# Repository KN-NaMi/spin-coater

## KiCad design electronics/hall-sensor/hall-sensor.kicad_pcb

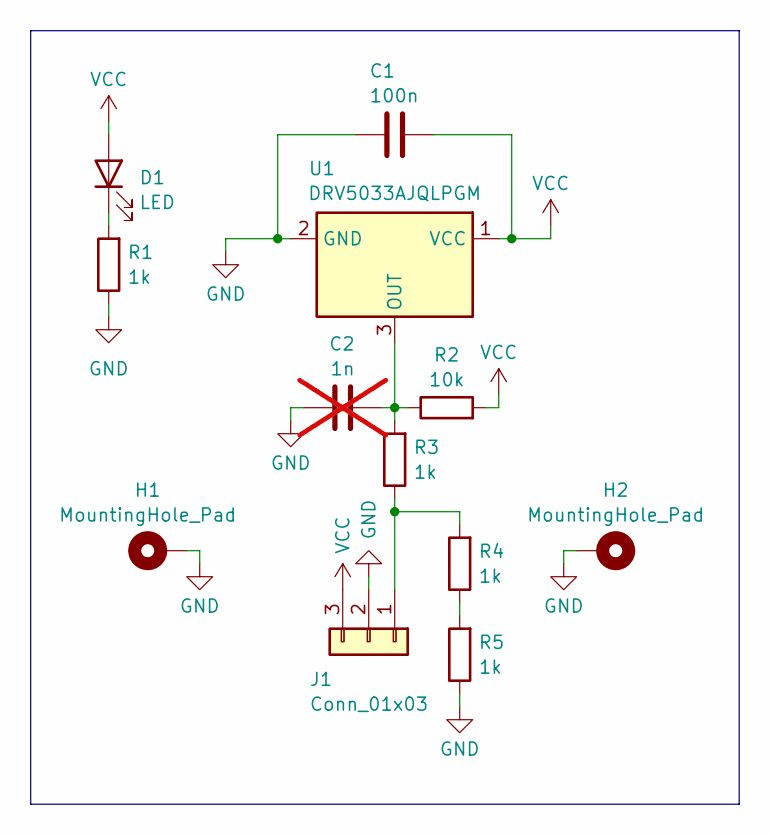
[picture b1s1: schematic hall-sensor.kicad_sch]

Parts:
C1: 100n; C_0805_2012Metric_Pad1.18x1.45mm_HandSolder
C2: 1n; C_0805_2012Metric_Pad1.18x1.45mm_HandSolder; not fitted
D1: LED; LED_1206_3216Metric
H1, H2: MountingHole_Pad; MountingHole_3.2mm_M3_Pad
J1: Conn_01x03; JST_XH_S3B-XH-A_1x03_P2.50mm_Horizontal
R1, R3, R4, R5: 1k; R_0805_2012Metric
R2: 10k; R_0805_2012Metric_Pad1.20x1.40mm_HandSolder
U1: DRV5033AJQLPGM; TO-92_Horizontal2

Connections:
GND: C1.2, C2.1, H1.1, H2.1, J1.2, R1.1, R5.1, U1.2 (GND)
unnamed: D1.1 (K), R1.2
unnamed: J1.1, R3.1, R4.2
unnamed: R4.1, R5.2
unnamed: C2.2, R2.1, R3.2, U1.3 (OUT)
VCC: C1.1, D1.2 (A), J1.3, R2.2, U1.1 (VCC)

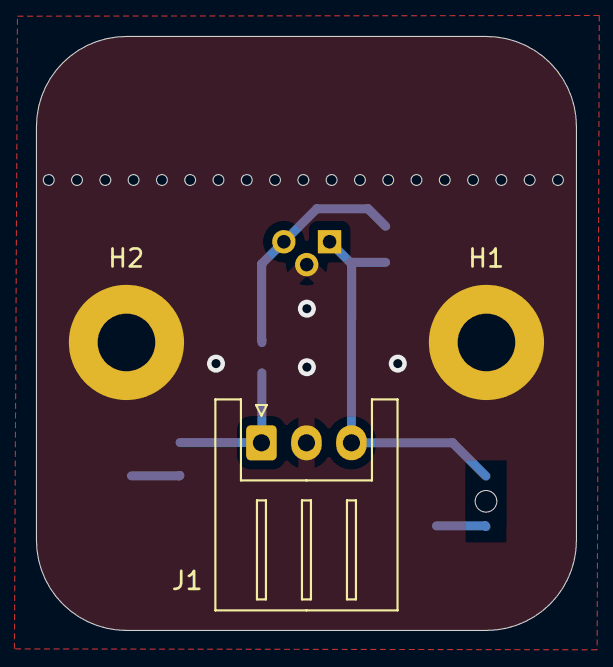
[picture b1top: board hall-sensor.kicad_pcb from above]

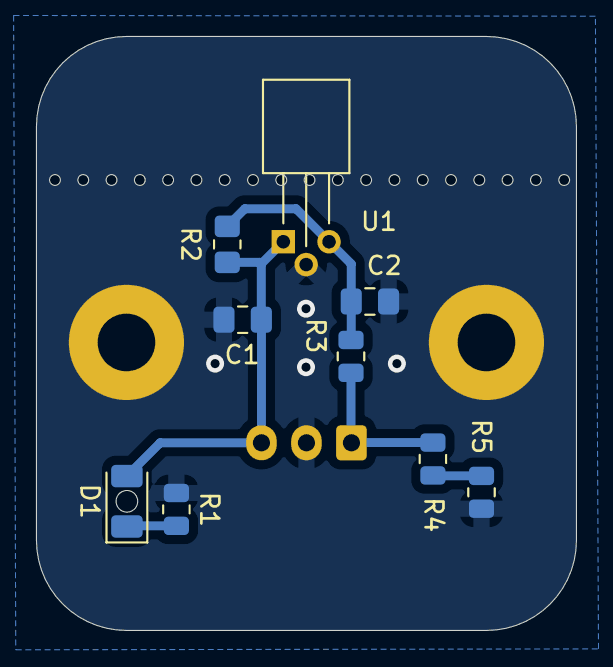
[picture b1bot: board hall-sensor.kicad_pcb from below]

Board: 2 copper layers, 30.0 x 33.0 mm, 12 parts (9 on the bottom side), 6 nets.

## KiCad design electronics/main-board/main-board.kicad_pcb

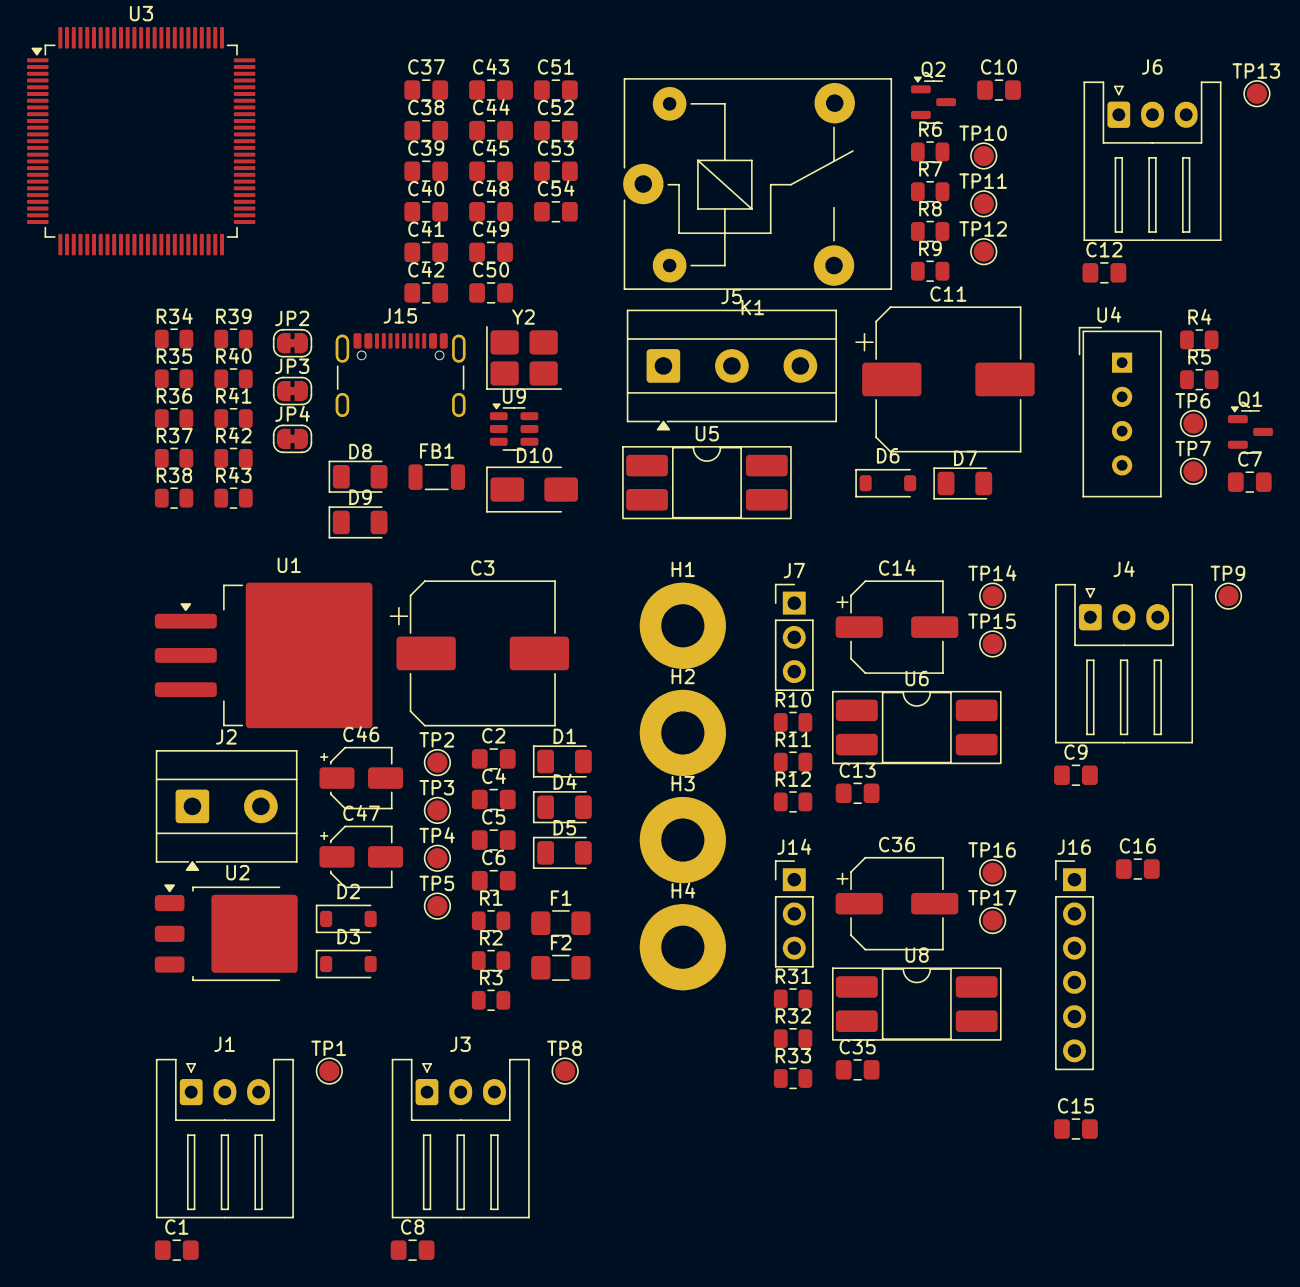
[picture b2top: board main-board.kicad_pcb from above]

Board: 2 copper layers, 120 parts (0 on the bottom side), 48 nets, no tracks yet.

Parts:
C1, C2, C4, C5, C6, C7, C8, C9, C10, C12, C13, C15, C16, C35, C37, C38, C39, C40, C41, C42, C43, C44, C45, C52: 100n; C_0805_2012Metric_Pad1.18x1.45mm_HandSolder
C3, C11: 220u; CP_Elec_10x10.5
C14, C36: 100u; CP_Elec_6.3x5.4
C46, C47: 10u; CP_Elec_4x5.4
C48, C49: 2n2; C_0805_2012Metric_Pad1.18x1.45mm_HandSolder
C50: 10p; C_0805_2012Metric_Pad1.18x1.45mm_HandSolder
C51: 20p; C_0805_2012Metric_Pad1.18x1.45mm_HandSolder
C53, C54: 470n; C_0805_2012Metric_Pad1.18x1.45mm_HandSolder
D1, D4, D5, D7, D8, D9: LED; LED_1206_3216Metric
D2, D3, D6: 1N4148W; D_SOD-123
D10: SS34; D_SMA
F1: 3A; Fuse_1206_3216Metric_Pad1.42x1.75mm_HandSolder
F2: 500mA; Fuse_1206_3216Metric_Pad1.42x1.75mm_HandSolder
FB1: FerriteBead; L_1206_3216Metric
H1, H2, H3, H4: MountingHole_Pad; MountingHole_3.2mm_M3_Pad
J1, J3, J4, J6: HALL-SENSOR; JST_XH_S3B-XH-A_1x03_P2.50mm_Horizontal
J2: 24V-IN; TerminalBlock_MetzConnect_Type101_RT01602HBWC_1x02_P5.08mm_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
J5: VACUME-PUMP; TerminalBlock_MetzConnect_Type101_RT01603HBWC_1x03_P5.08mm_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
J7, J14: SERVO_MOTOR-OUT; PinHeader_1x03_P2.54mm_Vertical
J15: SHOU HAN TYPE-C 16PIN 2MD; USB_C_Receptacle_GCT_USB4105-xx-A_16P_TopMnt_Horizontal
J16: UART; PinHeader_1x06_P2.54mm_Vertical
JP2, JP3, JP4: SolderJumper_2_Bridged; SolderJumper-2_P1.3mm_Bridged_RoundedPad1.0x1.5mm
K1: SRD-05VDC-SL-C; Relay_SPDT_SANYOU_SRD_Series_Form_C
Q1: BSS138; SOT-23
Q2: MMBT2222A; SOT-23
R1, R4, R5, R8, R9, R12, R33, R34, R35: 10k; R_0805_2012Metric
R2, R3, R7, R11, R32, R36, R37: 1k; R_0805_2012Metric
R6, R10, R31: 330; R_0805_2012Metric
R38, R39, R43: 0; R_0805_2012Metric
R40, R41: 5k1; R_0805_2012Metric
R42: 1M; R_0805_2012Metric
TP1, TP2, TP3, TP4, TP5, TP6, TP7, TP8, TP9, TP10, TP11, TP12, TP13, TP14, TP15, TP16, TP17: TestPoint; TestPoint_Pad_D1.5mm
U1: L7805; TO-263-3_TabPin2
U2: AMS1117CD-3.3; TO-252-3_TabPin2
U3: STM32F407V_E-G_Tx; LQFP-100_14x14mm_P0.5mm
U4: DHT11; Aosong_DHT11_5.5x12.0_P2.54mm
U5, U6, U8: EL817S1; DIP-4_W8.89mm_SMDSocket_LongPads
U9: SRV05-4; SOT-23-6
Y2: X322516MLB4SI; Crystal_SMD_3225-4Pin_3.2x2.5mm_HandSoldering

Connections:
+3V3: C1.2, C6.2, C8.2, C9.2, C12.2, C15.2, C16.2, C38.2, C39.2, C40.2, C41.2, C42.2, C43.2, C47.1, D3.2 (A), D5.2 (A), J1.1, J3.1, J4.1, J6.1, J16.2, J16.5, JP2.1 (A), JP3.1 (A), JP4.1 (A), Q1.1 (G), R4.2, R34.2, TP5.1, U2.2 (VO), U3.11 (VDD), U3.19 (VDD), U3.28 (VDD), U3.50 (VDD), U3.75 (VDD), U3.100 (VDD), U9.5 (VP)
+5V: C5.2, C7.2, C13.2, C14.1, C35.2, C36.1, C46.1, C53.2, D2.2 (A), D3.1 (K), D4.2 (A), D6.1 (K), J7.2, J14.2, K1.2, R5.2, R43.1, TP4.1, U1.3 (OUT), U2.3 (VI), U4.1 (VDD), U5.4, U6.4, U8.4
+24V: C10.2, C11.1, D1.2 (A), F1.2, K1.1, TP2.1
/DHT11/DHT11: Q1.2 (S), R4.1, TP6.1
/STM/BOOT: R35.2, U3.94 (BOOT0)
/STM/NRST: C37.2, R34.1, U3.14 (NRST)
/STM/USB_OTG_FS_DN: J15.A7 (D-), J15.B7 (D-), U3.70 (PA11), U9.3 (IO2), U9.6 (IO4)
/STM/USB_OTG_FS_DP: J15.A6 (D+), J15.B6 (D+), U3.71 (PA12), U9.1 (IO1), U9.4 (IO3)
/STM/VA: C45.2, FB1.2, U3.22 (VDDA)
/hall-sensor1/HALL: J1.3, TP1.1
/hall-sensor2/HALL: J3.3, TP8.1
/hall-sensor3/HALL: J6.3, TP13.1
/hall-sensor/HALL: J4.3, TP9.1
GND: C1.1, C2.1, C3.2, C4.1, C5.1, C6.1, C7.1, C8.1, C9.1, C10.1, C11.2, C12.1, C13.1, C14.2, C15.1, C16.1, C35.1, C36.2, C37.1, C38.1, C39.1, C40.1, C41.1, C42.1, C43.1, C44.1, C45.1, C46.2, C47.2, C48.1, C49.1, C50.1, C51.1, C52.1, C53.1, C54.1, H1.1, H2.1, H3.1, H4.1, J1.2, J2.1, J3.2, J4.2, J5.3, J6.2, J7.3, J14.3, J15.A1 (GND), J15.A12 (GND), J15.B1 (GND), J15.B12 (GND), J15.S1 (SHIELD), J16.1, J16.6, Q2.2 (E), R1.1, R2.1, R3.1, R8.2, R9.1, R12.2, R33.2, R35.1, R36.1, R37.1, R40.1, R41.1, U1.2 (GND), U2.1 (GND), U3.10 (VSS), U3.20 (VSSA), U3.27 (VSS), U3.74 (VSS), U3.99 (VSS), U4.4 (GND), U5.2, U6.2, U8.2, U9.2 (VN), Y2.2, Y2.4
unnamed: C50.2, R38.1, Y2.1
unnamed: C51.2, R39.1, Y2.3
unnamed: D1.1 (K), R1.2
unnamed: C4.2, D2.1 (K), F2.2, U1.1 (IN)
unnamed: D4.1 (K), R2.2
unnamed: D5.1 (K), R3.2
unnamed: D6.2 (A), K1.5, Q2.3 (C), TP10.1
unnamed: D7.2 (A), J5.1, K1.3
unnamed: D7.1 (K), R9.2
unnamed: D8.1 (K), R36.2
unnamed: D9.1 (K), R37.2
unnamed: D10.2 (A), J15.A4 (VBUS), J15.A9 (VBUS), J15.B4 (VBUS), J15.B9 (VBUS)
unnamed: C54.2, D10.1 (K), R43.2
unnamed: C2.2, C3.1, F1.1, F2.1, J2.2, TP3.1
unnamed: J5.2, K1.4
unnamed: J7.1, R11.2, R12.1, TP15.1
unnamed: J14.1, R32.2, R33.1, TP17.1
unnamed: J15.A5 (CC1), R41.2
unnamed: J15.B5 (CC2), R40.2
unnamed: Q1.3 (D), R5.1, TP7.1, U4.2 (DATA)
unnamed: Q2.1 (B), R7.2, R8.1, TP12.1
unnamed: R6.2, TP11.1, U5.1
unnamed: R7.1, U5.3
unnamed: R10.2, TP14.1, U6.1
unnamed: R11.1, U6.3
unnamed: R31.2, TP16.1, U8.1
unnamed: R32.1, U8.3
unnamed: R38.2, R42.1, U3.12 (PH0)
unnamed: R39.2, R42.2, U3.13 (PH1)
unnamed: C48.2, U3.49 (VCAP_1)
unnamed: C49.2, U3.73 (VCAP_2)
VBAT: C44.2, JP2.2 (B), U3.6 (VBAT)
VDDA: FB1.1, JP3.2 (B)
VREF: C52.2, JP4.2 (B), U3.21 (VREF+)

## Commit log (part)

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2025-10-29 init repo
2025-11-06 added manufacturer's .step of used motor
2025-11-06 Initial assembly of motor bracket
2025-11-06 moved parts & parameters to separate files
2025-11-06 added 608 bearing model & sources for .step's
2025-11-06 Moved motor mount assembly to separate folder
2025-11-08 Added main shaft assembly and GT2 Pulley parameteric
2025-11-08 updated README with roadmap
2025-11-13 Added schematic of prototype
2025-11-13 Added turntable and magnet mount
2025-11-15 Added complete assembly
2025-11-16 Clean untracked files according to .gitignore
2025-11-18 Fixed parametric pulley
2025-11-18 Added pulley tensioner
2025-11-18 Added splatter guide to complete assembly
2025-11-22 Moved Readme to Plane
2025-11-22 updated assembly to fit belt tensioner
2025-11-22 fixed parametric pulley again
2025-11-22 fixed fixed parametric pulley
2025-11-23 chore: moved .step to seperate folders
2025-11-23 feat: added vaccum version to spintable
2025-11-23 feat: added vacum PTFE tube adapter for testing
2025-11-23 feat: changed turntable to use TPU seal
2025-11-25 changed to ceramic bearings
2025-12-08 feat: changed main body to accept new bearings
2025-12-10 feat: tested v0.1 speed controler
2025-12-17 Added: software folder and first code
2026-01-21 added: Software folder and working code
2026-01-22 Added: Software folder and fully working code
2026-02-27 feat: moved Dorian_Branch to platformio
2026-02-27 feat: updated electronic schematic
2026-02-27 feat: modeled vaccum axile
2026-03-07 removed test files
2026-03-07 fixed schematic
2026-03-07 fixed code
2026-03-08 add hall sensor and main board
2026-03-10 voltage divider added for output pin of hall sensor
2026-03-14 feat: PID controller
2026-03-24 small tweak of mountig hole on hall-sensor board
2026-03-24 feat: updated prototype schematic
2026-05-11 added primitive enclosure
2026-05-21 safety commit
2026-05-21 generated print files
2026-06-14 temporary commit
2026-06-14 working PWM
2026-06-21 debug code for motor
